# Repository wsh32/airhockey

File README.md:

# airhockey
PIE Final - Air Hockey Playing Robot

Links to tutorials:
[Rosserial for Arduino](http://wiki.ros.org/rosserial_arduino/Tutorials/Arduino%20IDE%20Setup)

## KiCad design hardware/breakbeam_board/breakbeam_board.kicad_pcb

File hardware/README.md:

# Hardware

There are two PCBs we will design for this project. The first is a breakout
board for the [break beam
sensors](https://www.ttelectronics.com/TTElectronics/media/ProductFiles/Datasheets/OPB355-360to390-860to890.pdf). 
The second is an Arduino Mega shield that contains all of the required
circuitry.

### Setup

In KiCad, all the libraries are specified as project specific libraries. To use
this, you must first set up the git submodule for kicad-common.

```bash
git submodule init
git submodule update
```

Then, in KiCad, the `AIRHOCKEY_DIR` path must be configured. This should point
to the top level of the repository. For example, on my computer, it is
`/home/wsh32/git/airhockey`.

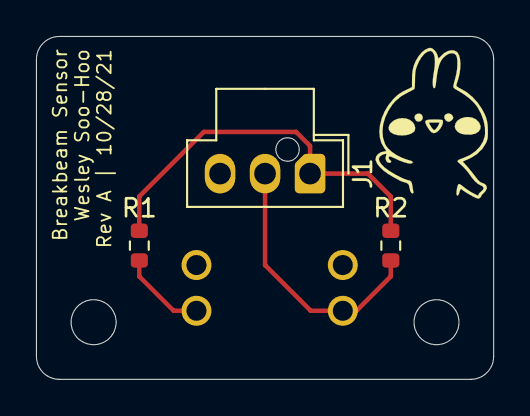
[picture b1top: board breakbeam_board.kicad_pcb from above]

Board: 2 copper layers, 25.4 x 19.1 mm, 4 parts (1 on the bottom side), 4 nets.

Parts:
J1: CONN; Molex_Nano-Fit_105309-xx03_1x03_P2.50mm_Vertical
R1: R_200; R_0603_1608Metric
R2: R_1M; R_0603_1608Metric
U1: OPB360N51

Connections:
/SIG: J1.2, R2.2, U1.3
GND: J1.3, U1.2, U1.4
unnamed: R1.2, U1.1
VCC: J1.1, R1.1, R2.1

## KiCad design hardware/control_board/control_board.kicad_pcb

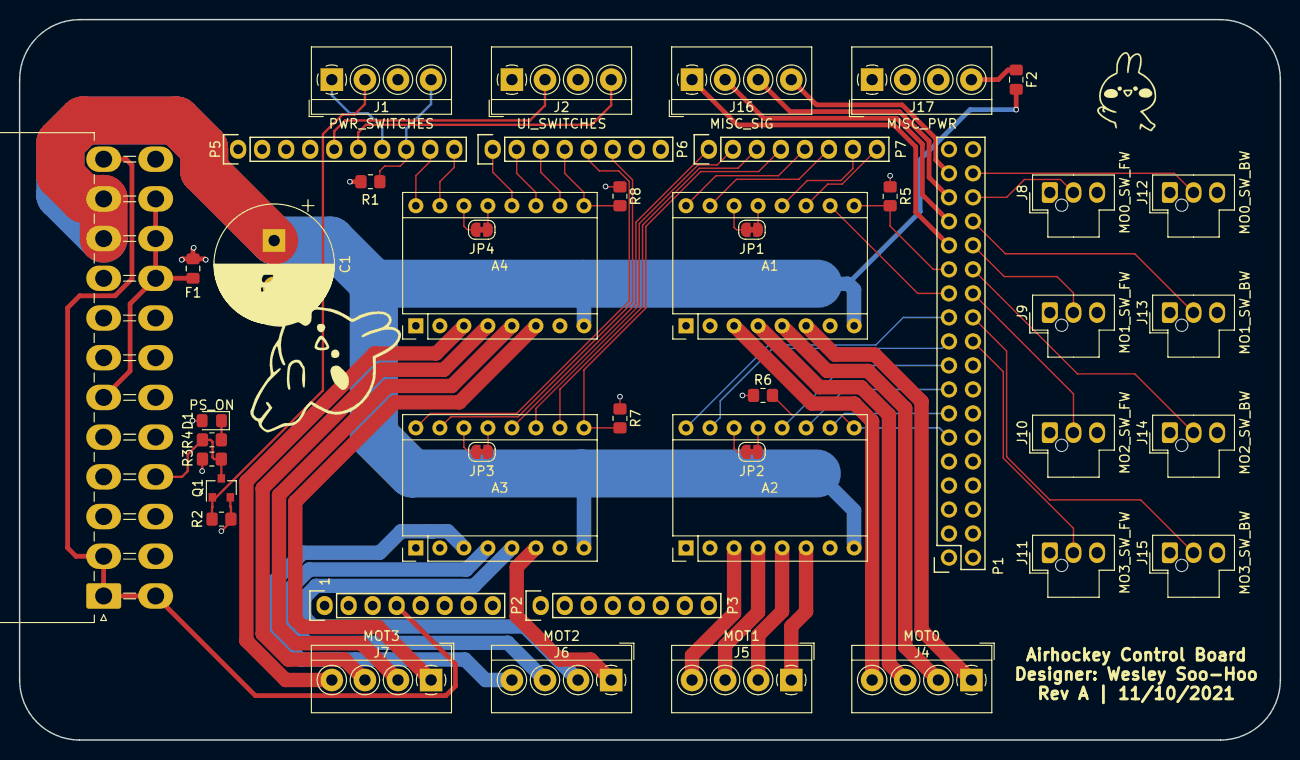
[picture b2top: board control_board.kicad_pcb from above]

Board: 4 copper layers, 133.3 x 76.2 mm, 44 parts (0 on the bottom side), 73 nets.

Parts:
A1, A2, A3, A4: Pololu_Breakout_A4988; Pololu_Breakout-16_15.2x20.3mm
C1: 100uF; CP_Radial_D12.5mm_P5.00mm
D1: PS_ON; LED_0805_2012Metric_Pad1.15x1.40mm_HandSolder
F1, F2: 1A; Fuse_0805_2012Metric_Pad1.15x1.40mm_HandSolder
J1: PWR_SWITCHES; TerminalBlock_4Ucon_1x04_P3.50mm_Horizontal
J2: UI_SWITCHES; TerminalBlock_4Ucon_1x04_P3.50mm_Horizontal
J3: ATX-24; Molex_Mini-Fit_Jr_5569-24A2_2x12_P4.20mm_Horizontal
J4: MOT0; TerminalBlock_4Ucon_1x04_P3.50mm_Horizontal
J5: MOT1; TerminalBlock_4Ucon_1x04_P3.50mm_Horizontal
J6: MOT2; TerminalBlock_4Ucon_1x04_P3.50mm_Horizontal
J7: MOT3; TerminalBlock_4Ucon_1x04_P3.50mm_Horizontal
J8: MO0_SW_FW; Molex_Nano-Fit_105309-xx03_1x03_P2.50mm_Vertical
J9: MO1_SW_FW; Molex_Nano-Fit_105309-xx03_1x03_P2.50mm_Vertical
J10: MO2_SW_FW; Molex_Nano-Fit_105309-xx03_1x03_P2.50mm_Vertical
J11: MO3_SW_FW; Molex_Nano-Fit_105309-xx03_1x03_P2.50mm_Vertical
J12: MO0_SW_BW; Molex_Nano-Fit_105309-xx03_1x03_P2.50mm_Vertical
J13: MO1_SW_BW; Molex_Nano-Fit_105309-xx03_1x03_P2.50mm_Vertical
J14: MO2_SW_BW; Molex_Nano-Fit_105309-xx03_1x03_P2.50mm_Vertical
J15: MO3_SW_BW; Molex_Nano-Fit_105309-xx03_1x03_P2.50mm_Vertical
J16: MISC_SIG; TerminalBlock_4Ucon_1x04_P3.50mm_Horizontal
J17: MISC_PWR; TerminalBlock_4Ucon_1x04_P3.50mm_Horizontal
JP1, JP2, JP3, JP4: NC; SolderJumper-2_P1.3mm_Bridged_RoundedPad1.0x1.5mm
P1: Digital; Socket_Strip_Arduino_2x18
P2: Power; Socket_Strip_Arduino_1x08
P3: Analog; Socket_Strip_Arduino_1x08
P5: PWM; Socket_Strip_Arduino_1x10
P6: PWM; Socket_Strip_Arduino_1x08
P7: Communication; Socket_Strip_Arduino_1x08
Q1: BSS138; SOT-23
R1, R2, R3, R5, R6, R7, R8: R_10K; R_0805_2012Metric_Pad1.20x1.40mm_HandSolder
R4: R_200; R_0805_2012Metric_Pad1.20x1.40mm_HandSolder

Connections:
+3V3: J3.1, J3.2, J3.12, J3.13, P2.4
+5V: A1.2, A2.2, A3.2, A4.2, D1.2, F1.1, J8.1, J9.1, J10.1, J11.1, J12.1, J13.1, J14.1, J15.1, J17.3, P1.35, P1.36, P2.5, R1.1, R3.1, R5.1, R6.1, R7.1, R8.1
+12V: A1.8, A2.8, A3.8, A4.8, C1.1, F2.2, J3.10, J3.11
/Connectors/5VPS: F1.2, J3.4, J3.6, J3.21, J3.22, J3.23
ESTOP_H: J1.2, Q1.1, R2.1
ESTOP_L: J1.1, P5.7
MISC_0: J16.1, P1.27
MISC_1: J16.2, P1.29
MISC_2: J16.3, P1.31
MISC_3: J16.4, P1.33
MOT0_1A: A1.4, J4.3
MOT0_1B: A1.3, J4.4
MOT0_2A: A1.5, J4.2
MOT0_2B: A1.6, J4.1
MOT0_DIR: A1.16, P7.5
MOT0_MS1: A1.10, P1.23
MOT0_MS2: A1.11, P7.8
MOT0_MS3: A1.12, P7.7
MOT0_STEP: A1.15, P7.6
MOT0_SWITCH_BW: J12.2, P1.34
MOT0_SWITCH_FW: J8.2, P1.32
MOT1_1A: A2.4, J5.3
MOT1_1B: A2.3, J5.4
MOT1_2A: A2.5, J5.2
MOT1_2B: A2.6, J5.1
MOT1_DIR: A2.16, P1.21
MOT1_MS1: A2.10, P1.13
MOT1_MS2: A2.11, P1.15
MOT1_MS3: A2.12, P1.17
MOT1_STEP: A2.15, P1.19
MOT1_SWITCH_BW: J13.2, P1.30
MOT1_SWITCH_FW: J9.2, P1.28
MOT2_1A: A3.4, J6.3
MOT2_1B: A3.3, J6.4
MOT2_2A: A3.5, J6.2
MOT2_2B: A3.6, J6.1
MOT2_DIR: A3.16, P6.5
MOT2_MS1: A3.10, P7.3
MOT2_MS2: A3.11, P7.2
MOT2_MS3: A3.12, P7.1
MOT2_STEP: A3.15, P6.6
MOT2_SWITCH_BW: J14.2, P1.26
MOT2_SWITCH_FW: J10.2, P1.24
MOT3_1A: A4.4, J7.3
MOT3_1B: A4.3, J7.4
MOT3_2A: A4.5, J7.2
MOT3_2B: A4.6, J7.1
MOT3_DIR: A4.16, P5.9
MOT3_MS1: A4.10, P6.3
MOT3_MS2: A4.11, P6.2
MOT3_MS3: A4.12, P6.1
MOT3_STEP: A4.15, P5.10
MOT3_SWITCH_BW: J15.2, P1.22
MOT3_SWITCH_FW: J11.2, P1.20
unnamed: A1.13, JP1.2
unnamed: A1.14, JP1.1
unnamed: A2.13, JP2.2
unnamed: A2.14, JP2.1
unnamed: A3.13, JP3.2
unnamed: A3.14, JP3.1
unnamed: A4.13, JP4.2
unnamed: A4.14, JP4.1
unnamed: D1.1, R4.1
unnamed: F2.1, J17.4
PWR_SW: J1.4, P5.8, R1.2
PWR_SW_L: A1.1, A1.7, A2.1, A2.7, A3.1, A3.7, A4.1, A4.7, C1.2, J1.3, J2.1, J2.3, J3.3, J3.5, J3.7, J3.15, J3.17, J3.18, J3.19, J3.24, J8.3, J9.3, J10.3, J11.3, J12.3, J13.3, J14.3, J15.3, J17.1, J17.2, P1.1, P1.2, P2.6, P2.7, P5.4, Q1.2, R2.2
UI_SWITCH_0: J2.4, P5.6
UI_SWITCH_1: J2.2, P5.5
~MOT0_EN: A1.9, P1.25, R5.2
~MOT1_EN: A2.9, P1.11, R6.2
~MOT2_EN: A3.9, P7.4, R7.2
~MOT3_EN: A4.9, P6.4, R8.2
~PS_ON: J3.16, Q1.3, R3.2, R4.2

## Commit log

2021-10-27 add opencv test scripts
2021-10-27 switch to using dev path for camera
2021-10-27 start ros structure
2021-10-28 camera launch file
2021-10-28 add default camera option
2021-10-28 start control board pcb
2021-10-28 Initialize puck tracking
2021-10-28 update gitignore
2021-10-28 add break beam board
2021-10-29 fix layout, add mimi and clean up silkscreen
2021-10-29 apriltag ros integration
2021-10-29 refactor to the apriltag node instead of a vision node
2021-10-30 Update puck HSV coloring
2021-10-30 update camera quality to improve speed
2021-10-30 add color argument for pucks
2021-10-30 added message for the apriltag detections
2021-11-01 fix ros custom messages, fully integration apriltag detections. tag family currently doesnt work because of iffy ros string support
2021-11-01 get tag family to work
2021-11-01 integrate puck tracking into ros
2021-11-01 use StepperDriver library
2021-11-01 Integrate april tag with puck tracking
2021-11-01 create launch file for all vision nodes
2021-11-02 add parameter files, add script to take a picture
2021-11-02 add bag file documentation
2021-11-02 separate out ros node from functional code
2021-11-02 add parameters to apriltags, add default values for puck tracker
2021-11-02 start adding unit tests
2021-11-02 add blue config file
2021-11-02 add test for blue config file
2021-11-02 start adding apriltag tests
2021-11-02 pytest github action
2021-11-02 remove catkin_build
2021-11-02 add pytest installation
2021-11-02 cleanup pytest action
2021-11-02 add cv_bridge as a dependency
2021-11-02 add python packages to package.xml
2021-11-02 add comment action
2021-11-02 add install requirements.txt, fix comment
2021-11-02 make sure puck tracking node always publishes frames
2021-11-02 remove testing on pull request
2021-11-03 drive motor and publish ROS
2021-11-03 create launch file for rosserial
2021-11-03 init physics package
2021-11-03 send custom data over ros
2021-11-03 add subscribe functionality to toggle motor
2021-11-04 create arduino makefile, reorganize firmware package
2021-11-04 add documentation for building and flashing arduino
2021-11-04 refactor to airhockey_firmware
2021-11-04 cleanup and change message names
2021-11-04 refactor arduino code, fix launch file to use the right port
2021-11-04 glue code, integration works
2021-11-04 add microstepping
2021-11-04 glue node
2021-11-04 add bag plot
2021-11-04 hacky visualization
2021-11-06 control board schematic
2021-11-06 update ui control pins
2021-11-06 control board pdf
2021-11-06 apriltag node reports actual corner positions
2021-11-08 begin puck trajectory
2021-11-09 make work as a standalone file with rosparam
2021-11-10 fix config files
2021-11-10 add ps on led
2021-11-10 add misc connectors
2021-11-11 finish layout, add fusing
2021-11-11 update kicad-common
2021-11-11 add fusing to layout
2021-11-11 start homography node
2021-11-11 add hooks in for ros
2021-11-11 simplify rosparam setting
2021-11-12 add homography math and tests
2021-11-12 fix homography
2021-11-12 add inverse homography function
2021-11-12 fix headers
2021-11-13 fix pytest
2021-11-13 fix puck tracker config files
2021-11-13 refactor tests
2021-11-13 fix homography, add homography matrix message
2021-11-15 fix rosparam loading
2021-11-16 Add trajectory files
2021-11-16 add new blue config for the light blue matte vinyl pucks
2021-11-16 update default config file to check for blue
2021-11-16 correct publish topic
2021-11-17 Update code in response to feedback
2021-11-18 start planner node
2021-11-18 cleanup
2021-11-18 fix missing trace
2021-11-18 cleanup unit tests
2021-11-18 deliberately break pytest
2021-11-18 take out tee
2021-11-18 update unit tests
2021-11-18 re-fix unit tests
2021-11-19 add table locations and reflections
2021-11-28 create one axis file
2021-11-28 update position to function from flexystepper
2021-11-29 Set theme jekyll-theme-cayman
2021-11-29 begin state machine
2021-11-30 implment striker position calculations
2021-11-30 fix directionality of relative puck motion
2021-12-01 add pinouts and begin defining states
2021-12-01 add rosparams to trajectory prediction
2021-12-02 ready for test
2021-12-02 change ROS subscribe message type
2021-12-02 has error with ros
2021-12-02 update libraries
2021-12-03 implement planner node hooks
2021-12-04 update for 1d arduino mega
2021-12-05 reorganize files and start to address comments
2021-12-05 add node and launch files for trajectory andplanner
2021-12-05 change necessary comments for test
2021-12-05 bring back makefile
2021-12-05 add setters
2021-12-05 minor adjustments
2021-12-06 Create index.html
    making website
2021-12-06 add testing using serial
2021-12-08 change homing to active high
2021-12-08 minor changes
2021-12-08 add debugging files, edit flexystepper to correct homing seq
2021-12-08 change header
2021-12-08 update state machine, add tests
2021-12-09 functional serial
2021-12-10 gete ROS over terminal functional
2021-12-11 Add HTML5 Up template
2021-12-11 start updating index
2021-12-11 remove index.html
2021-12-11 update ros_lib
2021-12-11 bug fixes, add all launch files, set focus to inf
2021-12-11 cleanup state machine, add power switch debouncing
2021-12-11 fix puck input message
2021-12-11 temporarily make controller follow puck state
2021-12-11 fix blue hsv values
2021-12-11 start filling out template
2021-12-12 clamp x pos values to min and max
2021-12-12 fix homing
2021-12-12 small cleanups in controlnode
2021-12-12 add puck position filter, test with puck matching
2021-12-12 change units to mm
2021-12-12 add accelstepper support
2021-12-12 add serial for accel
2021-12-13 Update about page + create new pages
2021-12-13 add images
2021-12-13 make all units consistent, fix reflections
2021-12-13 fix speeds and thresholds
2021-12-13 change folder name
2021-12-13 add headshots
2021-12-13 add y to arduino
2021-12-14 update website
2021-12-14 Finalize website
2021-12-14 fix minor typos
2021-12-14 add video
2022-01-06 Committing so I can pin this repo
